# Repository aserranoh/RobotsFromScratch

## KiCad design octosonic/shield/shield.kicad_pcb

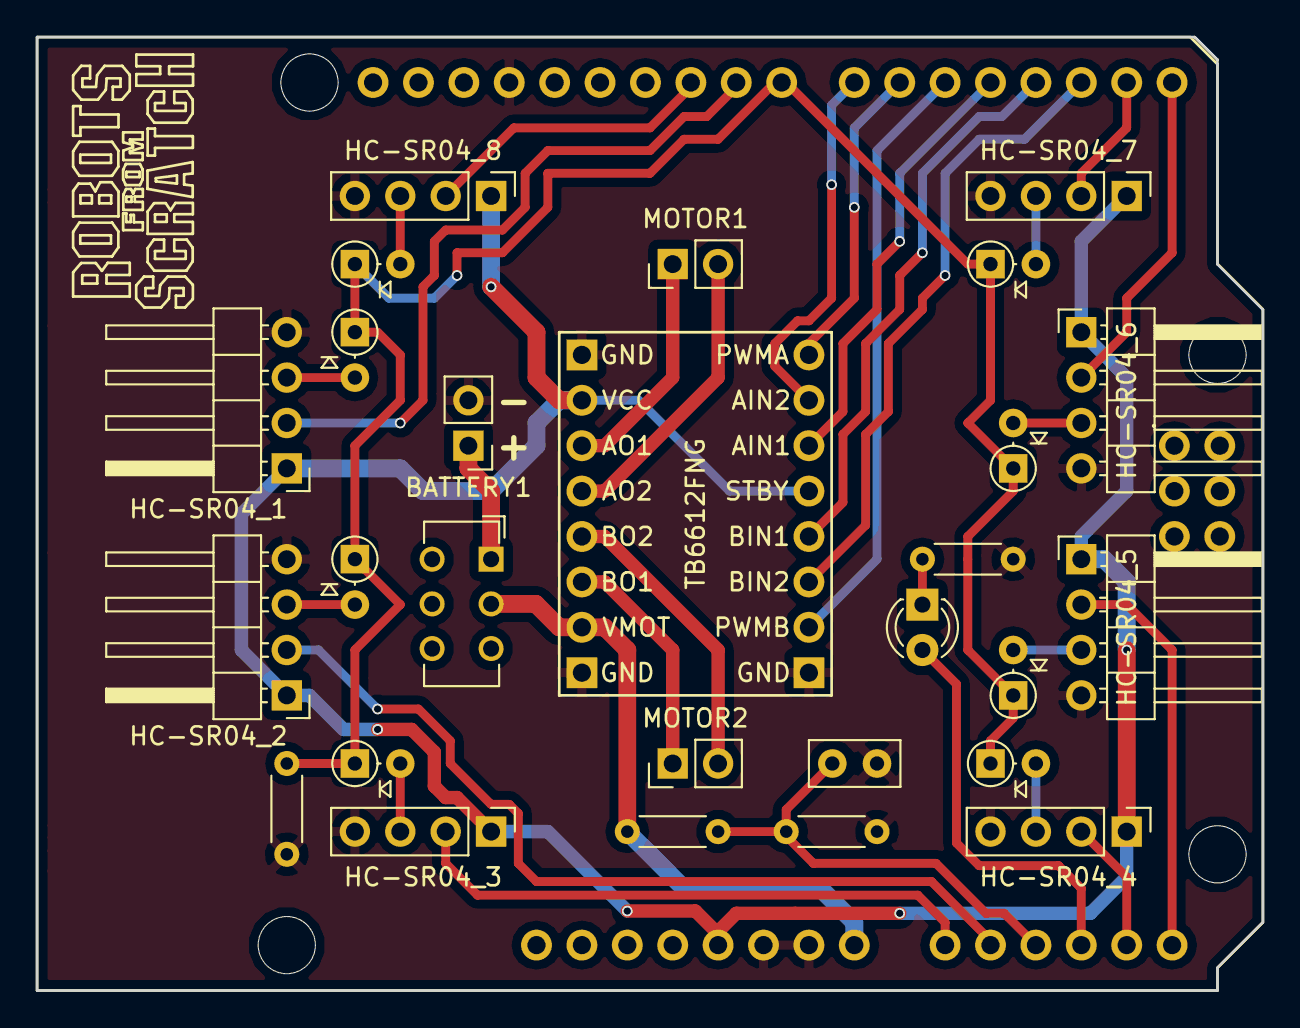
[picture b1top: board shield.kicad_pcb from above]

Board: 2 copper layers, 68.6 x 53.3 mm, 28 parts (0 on the bottom side), 34 nets.

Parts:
BATTERY1: Conn_01x02; Pin_Header_Straight_1x02_Pitch2.54mm
C1: 0.1uF; C_Disc_D5.0mm_W2.5mm_P2.50mm
D1, D2, D3, D4, D5, D6, D7, D8: 1N4148; D_DO-35_SOD27_P2.54mm_Vertical_AnodeUp
D9: LED_ALT; LED_D3.0mm
HC-SR04_1, HC-SR04_2, HC-SR04_5, HC-SR04_6: *; Pin_Header_Angled_1x04_Pitch2.54mm
HC-SR04_3, HC-SR04_4, HC-SR04_7, HC-SR04_8: *; Pin_Header_Straight_1x04_Pitch2.54mm
MOTOR1, MOTOR2: Conn_01x02; Pin_Header_Straight_1x02_Pitch2.54mm
R1: 5K; R_Axial_DIN0204_L3.6mm_D1.6mm_P5.08mm_Horizontal
R2, R3: 10M; R_Axial_DIN0204_L3.6mm_D1.6mm_P5.08mm_Horizontal
R4: 220; R_Axial_DIN0204_L3.6mm_D1.6mm_P5.08mm_Horizontal
SW1: SW_DPST_x2; SW_CuK_JS202011CQN_DPDT_Straight
U1: TB6612FNG
XA1: Arduino_Uno_Shield

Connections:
+5V: HC-SR04_1.1, HC-SR04_2.1, HC-SR04_3.1, HC-SR04_4.1, HC-SR04_5.1, HC-SR04_6.1, HC-SR04_7.1, HC-SR04_8.1, U1.2, U1.13, XA1.5V1
GND: BATTERY1.2, C1.1, HC-SR04_1.4, HC-SR04_2.4, HC-SR04_3.4, HC-SR04_4.4, HC-SR04_5.4, HC-SR04_6.4, HC-SR04_7.4, HC-SR04_8.4, R1.1, R3.1, R4.1, U1.1, U1.8, U1.9, XA1.GND1, XA1.GND2, XA1.GND3
unnamed: BATTERY1.1, SW1.1
unnamed: C1.2, R2.1, R3.2, XA1.A2
unnamed: D1.1, D2.1, D3.1, D4.1, D5.1, D6.1, D7.1, D8.1, R1.2, XA1.D8
unnamed: D1.2, HC-SR04_6.3
unnamed: D2.2, HC-SR04_7.3
unnamed: D3.2, HC-SR04_5.3
unnamed: D4.2, HC-SR04_4.3
unnamed: D5.2, HC-SR04_2.3
unnamed: D6.2, HC-SR04_1.3
unnamed: D7.2, HC-SR04_8.3
unnamed: D8.2, HC-SR04_3.3
unnamed: D9.1, R4.2
unnamed: D9.2, XA1.A3
unnamed: HC-SR04_1.2, XA1.D9
unnamed: HC-SR04_2.2, XA1.A1
unnamed: HC-SR04_3.2, XA1.A0
unnamed: HC-SR04_4.2, XA1.A4
unnamed: HC-SR04_5.2, XA1.A5
unnamed: HC-SR04_6.2, XA1.D0
unnamed: HC-SR04_7.2, XA1.D1
unnamed: HC-SR04_8.2, XA1.D10
unnamed: MOTOR1.1, U1.3
unnamed: MOTOR1.2, U1.4
unnamed: MOTOR2.1, U1.6
unnamed: MOTOR2.2, U1.5
unnamed: R2.2, SW1.2, U1.7, XA1.VIN
unnamed: U1.10, XA1.D5
unnamed: U1.11, XA1.D2
unnamed: U1.12, XA1.D3
unnamed: U1.14, XA1.D4
unnamed: U1.15, XA1.D7
unnamed: U1.16, XA1.D6

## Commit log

2018-10-14 finished octosonic Arduino shield
2018-10-15 Preliminary version of BOM, corrections in octosonic.dxf.
2018-11-04 Added octosonic printed parts designs.
2019-08-03 Implemented usart module in rfsavr library.
2019-08-04 Added capture module to rfsavr library.
2019-08-05 start developement of ultrasonic module.
2019-09-03 development of tutorial ultrasonic and rfsavr library.
2019-09-04 implementation of ultrasonic1 tutorial and rfsavr library.
2019-09-07 Corrected octosonic models after first assembly.
2019-09-15 developement of ultrasonic tutorial and librfsavr.
2019-09-21 Finished implementation of ultrasonic1.c source code for the ultrasonic tutorial #1.
2019-09-21 Finished visual example for the ultrasonic tutorial #1 (ultrasonic1.py).
2022-06-19 deleted original idea for this repository
2022-06-19 first version of joystick-control-simulator example.
2022-06-26 joystick-base.png: * New joystick image. Dockerfile: * Added ENV variable for joystick ball color. joy.js: * Fixed bouncing on iOS Safari. * Improved graphics. joystick.py: * main.html is now a templ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
2022-06-27 Dockerfile: * Image based on alpine, using build image. Makefile: control.c: * New application in C. control.py: * Deleted Python application.
2022-07-02 Dockerfile: * New image FROM scratch, based on a binary compiled from C. Makefile: joystick.c: mongoose.c: mongoose.h: * New embedded webserver on C using mongoose. main.html: * Template using % nota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
2022-07-03 .gitignore: * Added gitignore file. Dockerfile: * Creating image FROM scratch (binary static compiled). Makefile: * Compiling binary statically. control.c: * Code reorganized. joystick.c: * Returning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
2022-07-05 Extracted common code to utils.c.
2023-07-01 Added led-lamp project files.
